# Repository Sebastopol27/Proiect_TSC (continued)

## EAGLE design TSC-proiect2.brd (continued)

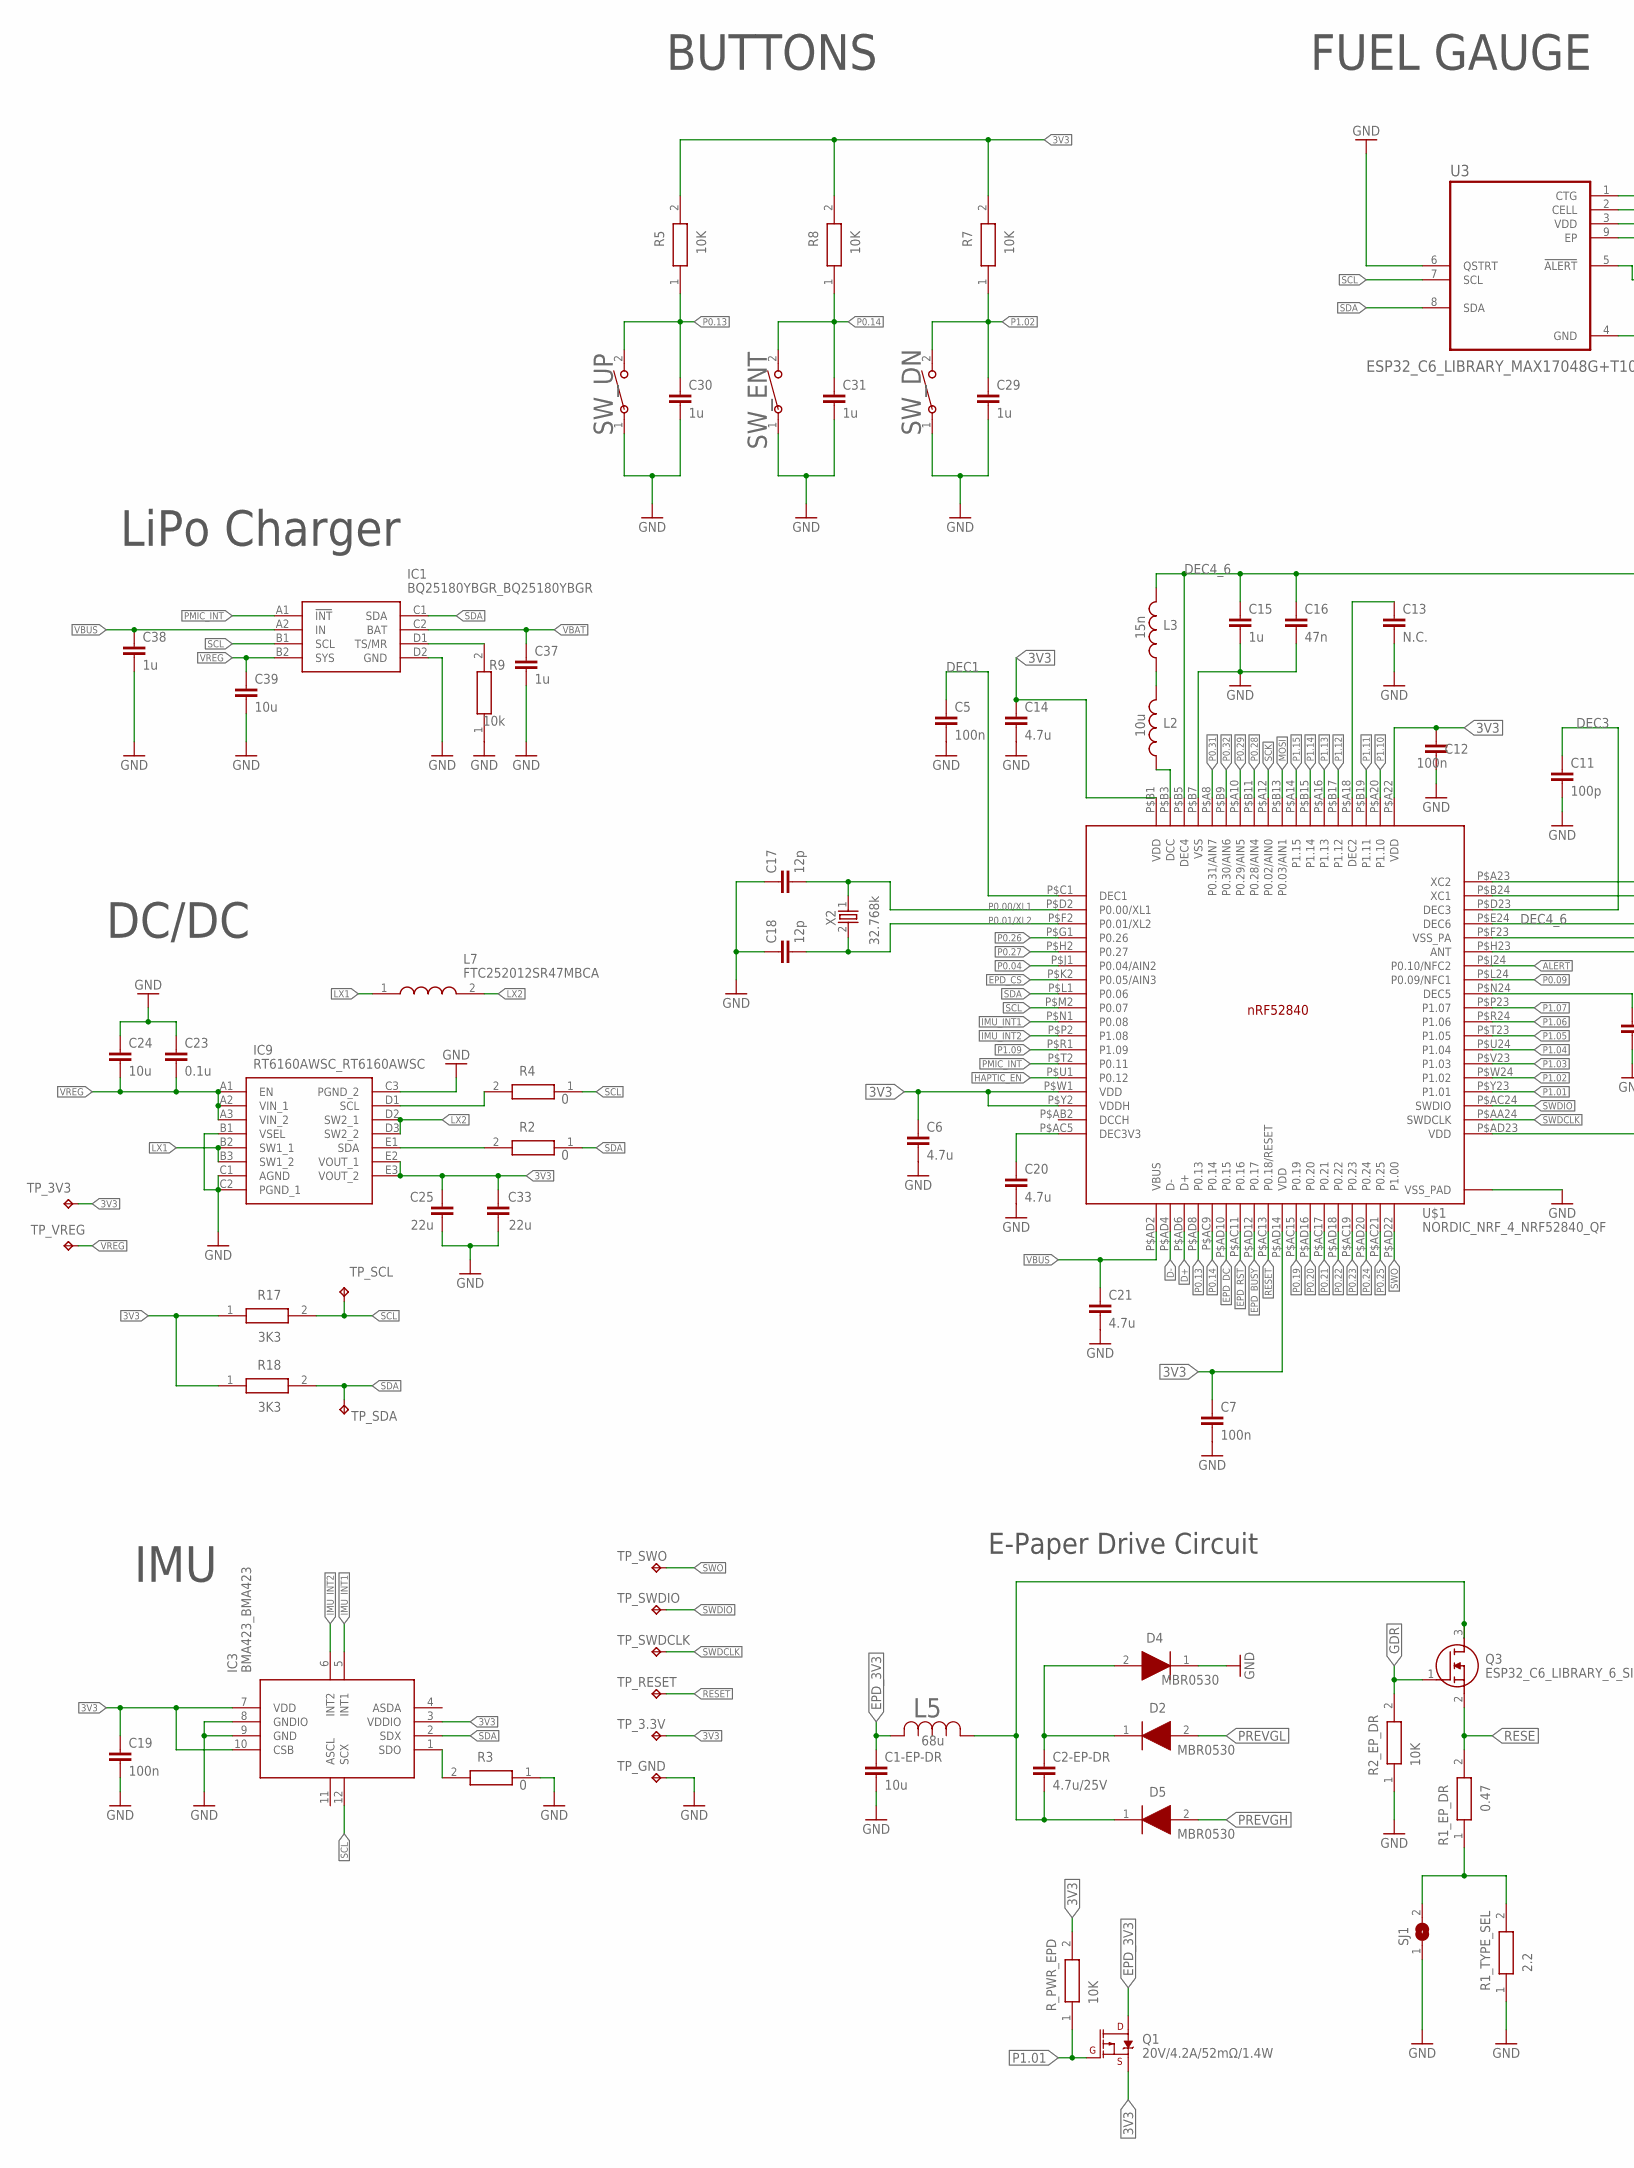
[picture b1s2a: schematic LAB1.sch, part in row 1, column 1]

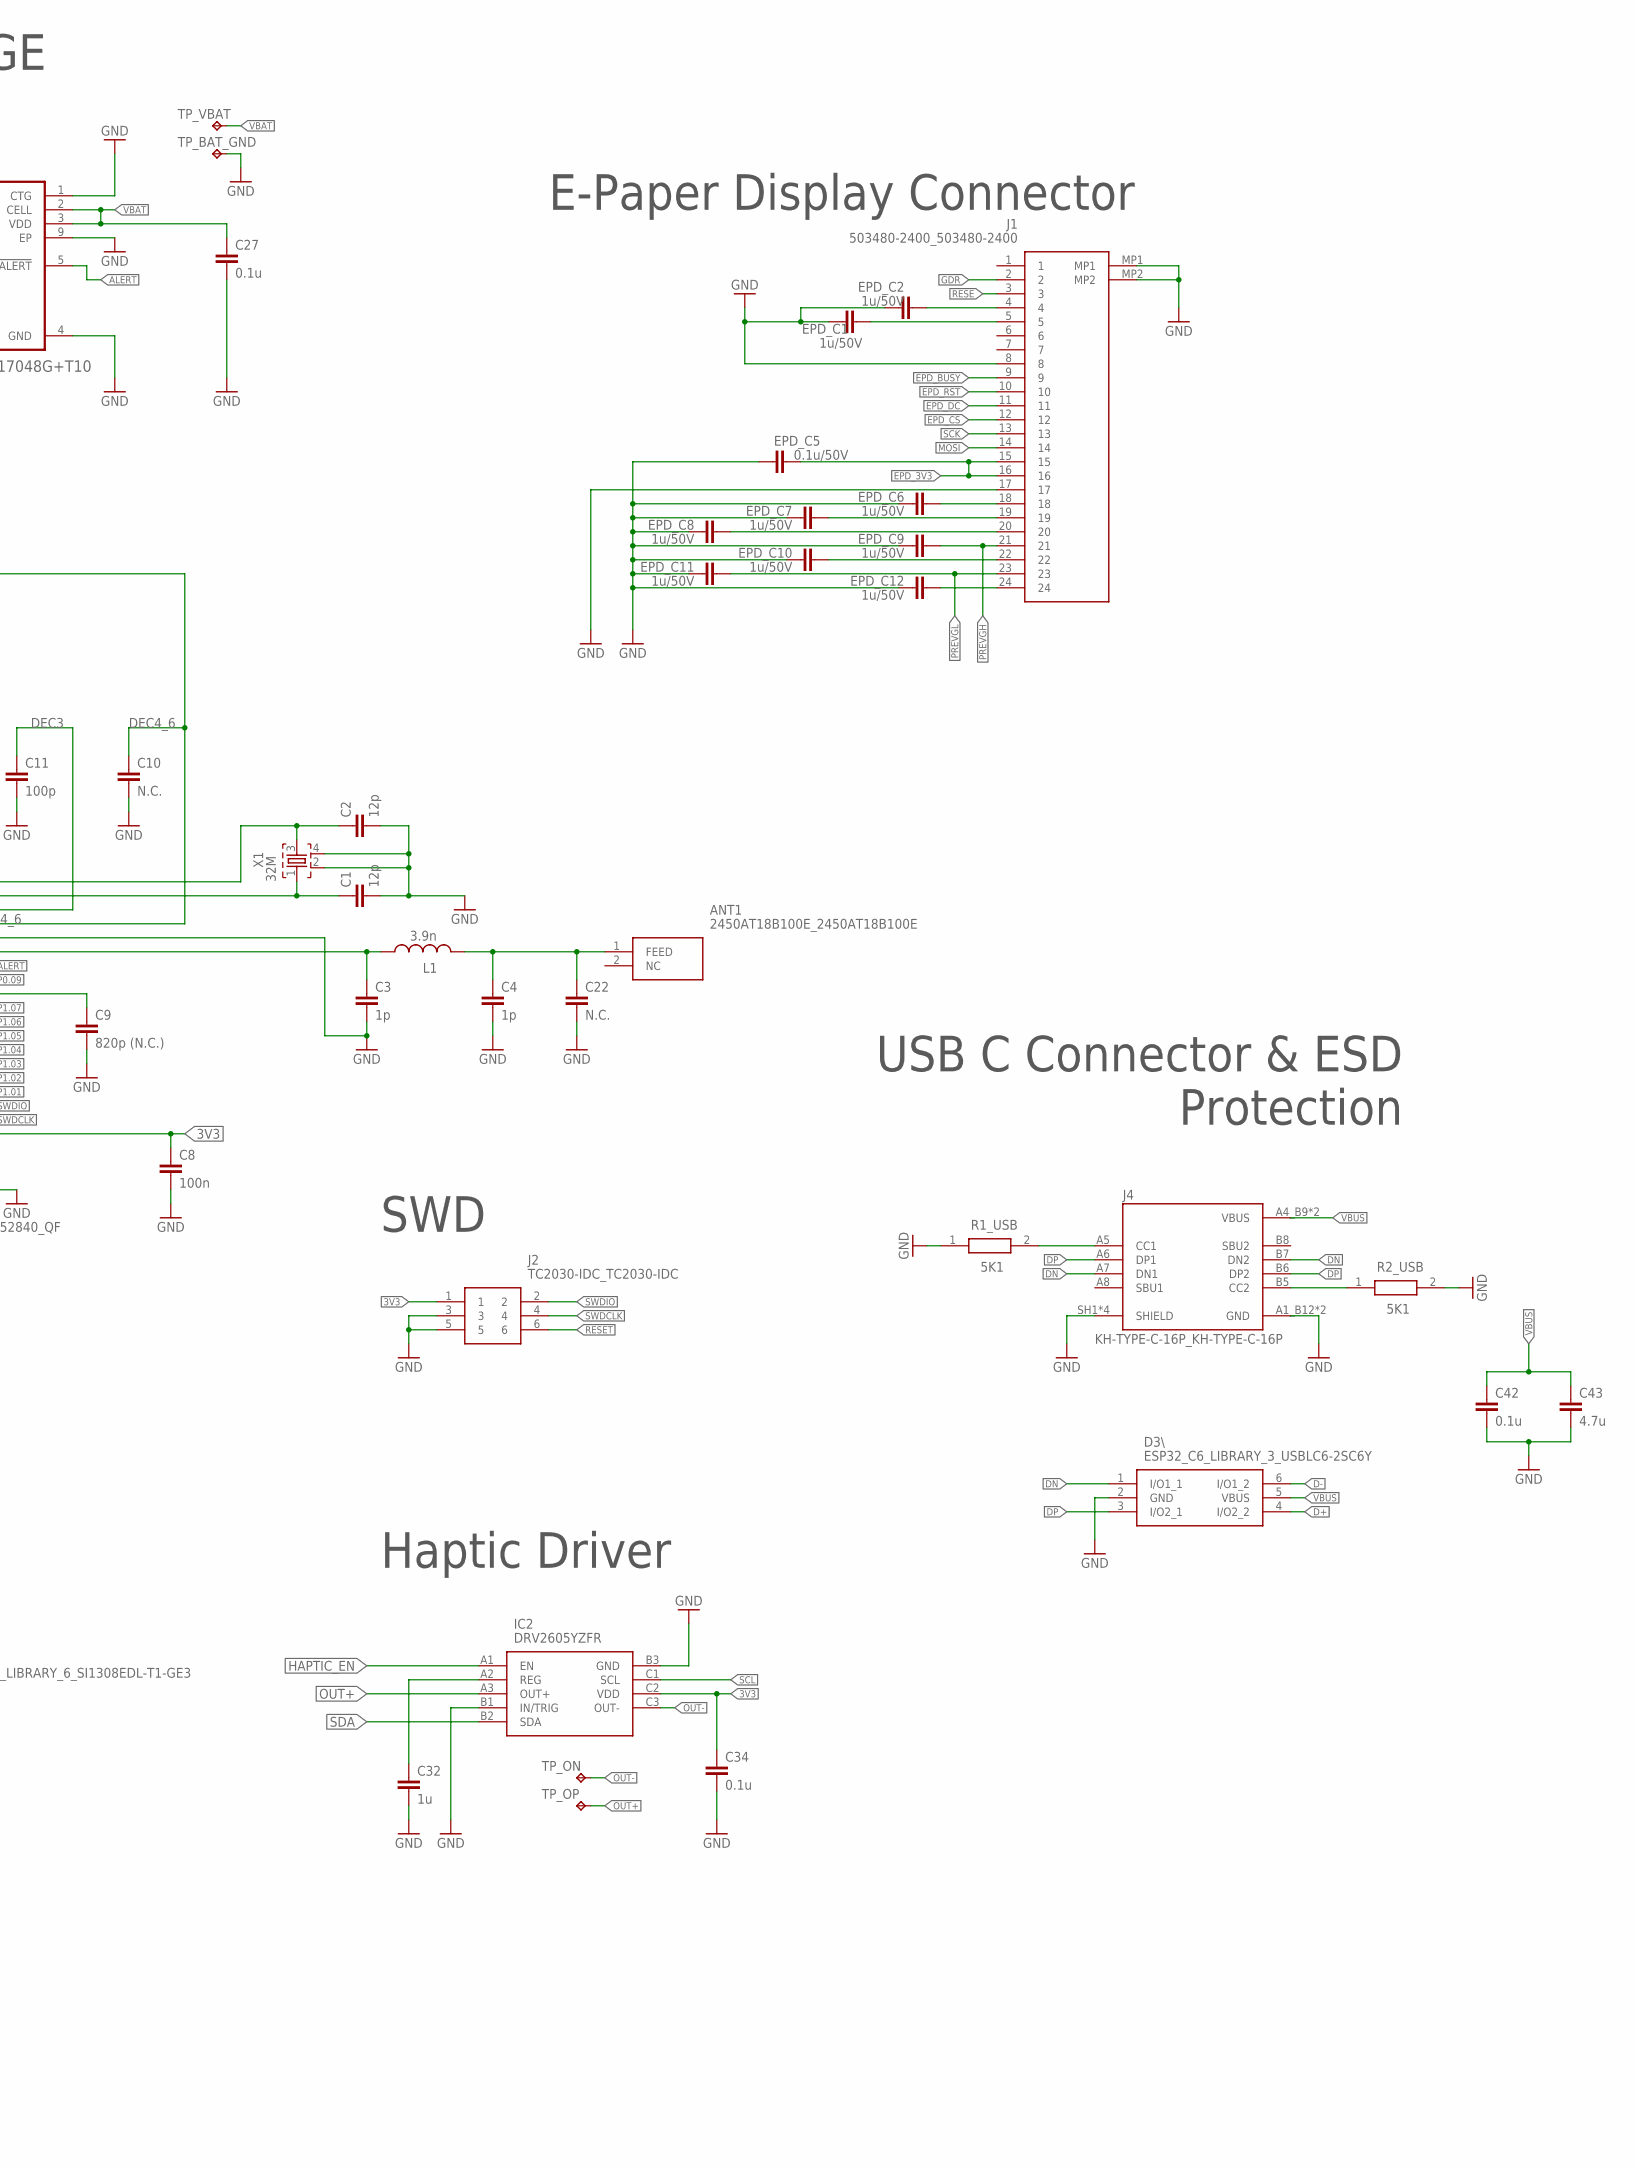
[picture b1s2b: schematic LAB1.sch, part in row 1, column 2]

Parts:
ANT1: 2450AT18B100E_2450AT18B100E; 2450AT18B100E_ANTC3216X140N
C1, C2, C17, C18: 12p; NORDIC_NRF_3_RESC0201_L
C1-EP-DR, C24, C39: 10u; PERFECT_0402_0402
C2-EP-DR: 4.7u/25V; NORDIC_NRF_3_RESC0603_L
C3, C4: 1p; NORDIC_NRF_3_RESC0201_L
C5, C7, C8, C12, C19: 100n; NORDIC_NRF_3_RESC0201_L
C6, C14, C20, C21, C43: 4.7u; PERFECT_0402_0402
C9: 820p (N.C.); NORDIC_NRF_3_RESC0201_L
C10, C22: N.C.; NORDIC_NRF_3_RESC0201_L
C11: 100p; NORDIC_NRF_3_RESC0201_L
C13: N.C.; PERFECT_0402_0402
C15, C29, C30, C31, C32, C37, C38: 1u; PERFECT_0402_0402
C16: 47n; NORDIC_NRF_3_RESC0201_L
C23, C27, C34, C42: 0.1u; NORDIC_NRF_3_RESC0201_L
C25: 22u; NORDIC_NRF_3_RESC0201_L
C33: 22u; PERFECT_0402_0402
D2, D4, D5: MBR0530; ESP32_C6_LIBRARY_5_SOD3716X135N
D3\: ESP32_C6_LIBRARY_3_USBLC6-2SC6Y; ESP32_C6_LIBRARY_3_SOT95P280X145-6N
EPD_C1, EPD_C2, EPD_C6, EPD_C7, EPD_C8, EPD_C9, EPD_C10, EPD_C11, EPD_C12: 1u/50V; NORDIC_NRF_3_RESC0603_L
EPD_C5: 0.1u/50V; NORDIC_NRF_3_RESC0603_L
IC1: BQ25180YBGR_BQ25180YBGR; BQ25180YBGR_BGA8C40P2X4_100X155X50
IC2: DRV2605YZFR; DRV2605YZFR_BGA9C50P3X3_144X144X62
IC3: BMA423_BMA423
IC9: RT6160AWSC_RT6160AWSC; RT6160AWSC_BGA15C40P3X5_140X230X60
J1: 503480-2400_503480-2400; 503480-2400_5034802400
J2: TC2030-IDC_TC2030-IDC; TC2030-IDC_TC2030IDC
J4: KH-TYPE-C-16P_KH-TYPE-C-16P; KH-TYPE-C-16P_KINGHELM_KH-TYPE-C-16P
L1: 3.9n; NORDIC_NRF_2_RESC0201_L
L2: 10u; NORDIC_NRF_2_RESC0402_L
L3: 15n; NORDIC_NRF_2_RESC0201_L
L5: 68u; ESP32_C6_LIBRARY_2_IND_4828-WE-TPC_WRE
L7: FTC252012SR47MBCA; MLP2016SR47MT0S1_INDC2016X100N
Q1: 20V/4.2A/52mΩ/1.4W; ESP32_C6_LIBRARY_4_ESP32_C6_LIBRARY_4_ESP32_C6_LIBRARY_4_ES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
Q3: ESP32_C6_LIBRARY_6_SI1308EDL-T1-GE3; ESP32_C6_LIBRARY_6_SOT65P210X110-3N
R1_EP_DR: 0.47; CPF0201D7K68C1_0201
R1_TYPE_SEL: 2.2; CPF0201D7K68C1_0201
R1_USB, R2_USB: 5K1; CPF0201D7K68C1_0201
R2, R3, R4: 0; CPF0201D7K68C1_0201
R2_EP_DR, R5, R7, R8: 10K; CPF0201D7K68C1_0201
R9: 10k; CPF0201D7K68C1_0201
R17, R18: 3K3; CPF0201D7K68C1_0201
R_PWR_EPD: 10K; CPF0201D7K68C1_0201
SJ1: ESP32_C6_LIBRARY_7_JUMPER_SJ
SW_DN: 2025-10-22_07-23-44_LIBRARY_EVP-AKE31ASW_EVP-AKE3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; 2025-10-22_07-23-44_LIBRARY_SW_EVP-AKE31A_PAN
SW_ENT: 2025-10-22_07-23-44_LIBRARY_EVP-AKE31ASW_EVP-AKE3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; 2025-10-22_07-23-44_LIBRARY_SW_EVP-AKE31A_PAN
SW_UP: 2025-10-22_07-23-44_LIBRARY_EVP-AKE31ASW_EVP-AKE3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; 2025-10-22_07-23-44_LIBRARY_SW_EVP-AKE31A_PAN
TP_3.3V, TP_3V3: HECTOR_WATCH_1_TPTP20R; HECTOR_WATCH_1_TP20R
TP_BAT_GND: HECTOR_WATCH_1_TPTP20R; HECTOR_WATCH_1_TP20R
TP_GND: HECTOR_WATCH_1_TPTP20R; HECTOR_WATCH_1_TP20R
TP_ON: HECTOR_WATCH_1_TPTP20R; HECTOR_WATCH_1_TP20R
TP_OP: HECTOR_WATCH_1_TPTP20R; HECTOR_WATCH_1_TP20R
TP_RESET: HECTOR_WATCH_1_TPTP20R; HECTOR_WATCH_1_TP20R
TP_SCL: HECTOR_WATCH_1_TPTP20R; HECTOR_WATCH_1_TP20R
TP_SDA: HECTOR_WATCH_1_TPTP20R; HECTOR_WATCH_1_TP20R
TP_SWDCLK: HECTOR_WATCH_1_TPTP20R; HECTOR_WATCH_1_TP20R
TP_SWDIO: HECTOR_WATCH_1_TPTP20R; HECTOR_WATCH_1_TP20R
TP_SWO: HECTOR_WATCH_1_TPTP20R; HECTOR_WATCH_1_TP20R
TP_VBAT: HECTOR_WATCH_1_TPTP20R; HECTOR_WATCH_1_TP20R
TP_VREG: HECTOR_WATCH_1_TPTP20R; HECTOR_WATCH_1_TP20R
U3: ESP32_C6_LIBRARY_MAX17048G+T10; ESP32_C6_LIBRARY_SON50P200X200X80-9N
U$1: NORDIC_NRF_4_NRF52840_QF; NORDIC_NRF_4_AQFN50P700X700X85_HS-74N
X1: 32M; NORDIC_NRF_BT-XTAL_2016_N
X2: 32.768k; NORDIC_NRF_1_XTAL_3215_N

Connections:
ALERT: U3.5 (!ALERT), U$1.P$J24 (P0.10/NFC2)
D+: D3\.4 (I/O2_2), U$1.P$AD6 (D+)
D-: D3\.6 (I/O1_2), U$1.P$AD4 (D-)
DEC1: C5.1, U$1.P$C1 (DEC1)
DEC3: C11.1, U$1.P$D23 (DEC3)
DEC4_6: C10.1, C15.1, C16.1, L3.2, U$1.P$B5 (DEC4), U$1.P$E24 (DEC6)
DN: D3\.1 (I/O1_1), J4.A7 (DN1), J4.B7 (DN2)
DP: D3\.3 (I/O2_1), J4.A6 (DP1), J4.B6 (DP2)
EPD_3V3: C1-EP-DR.1, EPD_C5.2, J1.15, J1.16, L5.2, Q1.3 (D)
EPD_BUSY: J1.9, U$1.P$AD12 (P0.17)
EPD_CS: J1.12, U$1.P$K2 (P0.05/AIN3)
EPD_DC: J1.11, U$1.P$AD10 (P0.15)
EPD_RST: J1.10, U$1.P$AC11 (P0.16)
GDR: J1.2, Q3.1 (G), R2_EP_DR.2
GND: C1.2, C1-EP-DR.2, C2.2, C3.2, C4.2, C5.2, C6.2, C7.2, C8.2, C9.2, C10.2, C11.2, C12.2, C13.2, C14.2, C15.2, C16.2, C17.1, C18.1, C19.2, C20.2, C21.2, C22.2, C23.1, C24.1, C25.1, C27.2, C29.2, C30.2, C31.2, C32.2, C33.1, C34.2, C37.2, C38.2, C39.2, C42.2, C43.2, D3\.2 (GND), D4.1 (K), EPD_C1.1, EPD_C2.1, EPD_C5.1, EPD_C6.1, EPD_C7.1, EPD_C8.1, EPD_C9.1, EPD_C10.1, EPD_C11.1, EPD_C12.1, IC1.D2 (GND), IC2.B1 (IN/TRIG), IC2.B3 (GND), IC3.8 (GNDIO), IC3.9 (GND), IC9.B1 (VSEL), IC9.C1 (AGND), IC9.C2 (PGND_1), IC9.C3 (PGND_2), J1.8, J1.17, J1.MP1, J1.MP2, J2.3, J2.5, J4.A1_B12 (GND), J4.A12_B1 (GND), J4.SH1 (SHIELD), J4.SH2 (SHIELD), J4.SH3 (SHIELD), J4.SH4 (SHIELD), R1_TYPE_SEL.1, R1_USB.1, R2_EP_DR.1, R2_USB.2, R3.1, R9.1, SJ1.1, SW_DN.1, SW_ENT.1, SW_UP.1, TP_BAT_GND.TP, TP_GND.TP, U3.1 (CTG), U3.4 (GND), U3.6 (QSTRT), U3.9 (EP), U$1.P$74 (VSS_PAD), U$1.P$75 (VSS_PAD), U$1.P$76 (VSS_PAD), U$1.P$77 (VSS_PAD), U$1.P$78 (VSS_PAD), U$1.P$79 (VSS_PAD), U$1.P$80 (VSS_PAD), U$1.P$81 (VSS_PAD), U$1.P$82 (VSS_PAD), U$1.P$83 (VSS_PAD), U$1.P$84 (VSS_PAD), U$1.P$85 (VSS_PAD), U$1.P$86 (VSS_PAD), U$1.P$87 (VSS_PAD), U$1.P$88 (VSS_PAD), U$1.P$89 (VSS_PAD), U$1.P$90 (VSS_PAD), U$1.P$B7 (VSS), U$1.P$F23 (VSS_PA), X1.2, X1.4
HAPTIC_EN: IC2.A1 (EN), U$1.P$U1 (P0.12)
IMU_INT1: IC3.5 (INT1), U$1.P$N1 (P0.08)
IMU_INT2: IC3.6 (INT2), U$1.P$P2 (P1.08)
LX1: IC9.B2 (SW1_1), IC9.B3 (SW1_2), L7.1
LX2: IC9.D2 (SW2_1), IC9.D3 (SW2_2), L7.2
MOSI: J1.14, U$1.P$B13 (P0.03/AIN1)
unnamed: L2.1, U$1.P$B3 (DCC)
unnamed: L2.2, L3.1
unnamed: C13.1, U$1.P$A18 (DEC2)
unnamed: C20.1, U$1.P$AC5 (DEC3V3)
unnamed: C9.1, U$1.P$N24 (DEC5)
unnamed: C3.1, L1.1, U$1.P$H23 (ANT)
unnamed: ANT1.1 (FEED), C4.1, C22.1, L1.2
unnamed: C1.1, U$1.P$B24 (XC1), X1.1
unnamed: C2.1, U$1.P$A23 (XC2), X1.3
unnamed: IC1.D1 (TS/MR), R9.2
unnamed: IC9.D1 (SCL), R4.2
unnamed: IC9.E1 (SDA), R2.2
unnamed: R17.1, R18.1
unnamed: R1_EP_DR.1, R1_TYPE_SEL.2, SJ1.2
unnamed: C32.1, IC2.A2 (REG)
unnamed: C2-EP-DR.1, D2.1 (K), D4.2 (A)
unnamed: C2-EP-DR.2, D5.1 (K), L5.1, Q3.3 (D)
unnamed: IC3.1 (SDO), R3.2
unnamed: EPD_C6.2, J1.18
unnamed: EPD_C7.2, J1.19
unnamed: EPD_C2.2, J1.4
unnamed: EPD_C1.2, J1.5
unnamed: EPD_C8.2, J1.20
unnamed: EPD_C10.2, J1.22
unnamed: EPD_C12.2, J1.24
unnamed: J4.B5 (CC2), R2_USB.1
unnamed: J4.A5 (CC1), R1_USB.2
OUT+: IC2.A3 (OUT+), TP_OP.TP
OUT-: IC2.C3 (OUT-), TP_ON.TP
P0.00/XL1: C17.2, U$1.P$D2 (P0.00/XL1), X2.1
P0.01/XL2: C18.2, U$1.P$F2 (P0.01/XL2), X2.2
P0.04: U$1.P$J1 (P0.04/AIN2)
P0.09: U$1.P$L24 (P0.09/NFC1)
P0.13: C30.1, R5.1, SW_UP.2, U$1.P$AD8 (P0.13)
P0.14: C31.1, R8.1, SW_ENT.2, U$1.P$AC9 (P0.14)
P0.19: U$1.P$AC15 (P0.19)
P0.20: U$1.P$AD16 (P0.20)
P0.21: U$1.P$AC17 (P0.21)
P0.22: U$1.P$AD18 (P0.22)
P0.23: U$1.P$AC19 (P0.23)
P0.24: U$1.P$AD20 (P0.24)
P0.25: U$1.P$AC21 (P0.25)
P0.26: U$1.P$G1 (P0.26)
P0.27: U$1.P$H2 (P0.27)
P0.28: U$1.P$B11 (P0.28/AIN4)
P0.29: U$1.P$A10 (P0.29/AIN5)
P0.31: U$1.P$A8 (P0.31/AIN7)
P0.32: U$1.P$B9 (P0.30/AIN6)
P1.01: Q1.1 (G), R_PWR_EPD.1, U$1.P$Y23 (P1.01)
P1.02: C29.1, R7.1, SW_DN.2, U$1.P$W24 (P1.02)
P1.03: U$1.P$V23 (P1.03)
P1.04: U$1.P$U24 (P1.04)
P1.05: U$1.P$T23 (P1.05)
P1.06: U$1.P$R24 (P1.06)
P1.07: U$1.P$P23 (P1.07)
P1.09: U$1.P$R1 (P1.09)
P1.10: U$1.P$A20 (P1.10)
P1.11: U$1.P$B19 (P1.11)
P1.12: U$1.P$B17 (P1.12)
P1.13: U$1.P$A16 (P1.13)
P1.14: U$1.P$B15 (P1.14)
P1.15: U$1.P$A14 (P1.15)
PMIC_INT: IC1.A1 (!INT), U$1.P$T2 (P0.11)
PREVGH: D5.2 (A), EPD_C9.2, J1.21
PREVGL: D2.2 (A), EPD_C11.2, J1.23
RESE: J1.3, Q3.2 (S), R1_EP_DR.2
RESET: J2.6, TP_RESET.TP, U$1.P$AC13 (P0.18/RESET)
SCK: J1.13, U$1.P$A12 (P0.02/AIN0)
SWDCLK: J2.4, TP_SWDCLK.TP, U$1.P$AA24 (SWDCLK)
SWDIO: J2.2, TP_SWDIO.TP, U$1.P$AC24 (SWDIO)
SWO: TP_SWO.TP, U$1.P$AD22 (P1.00)
VBAT: C27.1, C37.1, IC1.C2 (BAT), TP_VBAT.TP, U3.2 (CELL), U3.3 (VDD)
VBUS: C21.1, C38.1, C42.1, C43.1, D3\.5 (VBUS), IC1.A2 (IN), J4.A4_B9 (VBUS), J4.A9_B4 (VBUS), U$1.P$AD2 (VBUS)
VREG: C23.2, C24.2, C39.1, IC1.B2 (SYS), IC9.A1 (EN), IC9.A2 (VIN_1), IC9.A3 (VIN_2), TP_VREG.TP

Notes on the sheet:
LiPo Charger
DC/DC
IMU
SWD
E-Paper Drive Circuit
Haptic Driver
BUTTONS
FUEL GAUGE
E-Paper Display Connector
USB C Connector & ESD Protection

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
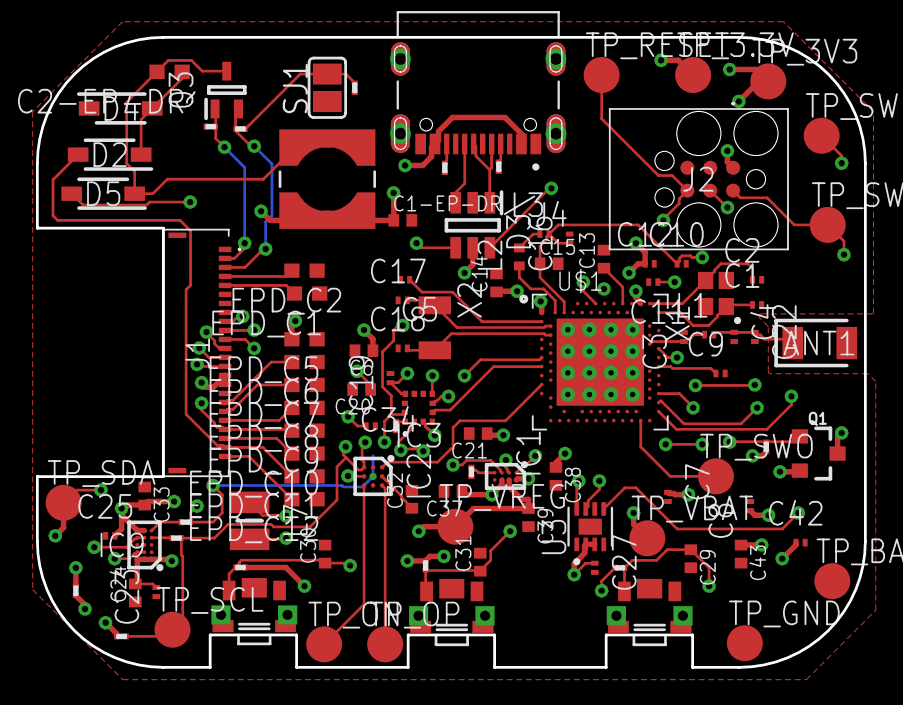
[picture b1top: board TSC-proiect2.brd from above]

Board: 4 copper layers, 46.0 x 35.0 mm, 105 parts (0 on the bottom side), 71 nets.

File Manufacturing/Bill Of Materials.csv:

Reference Designators;Quantity;Description;Package;Value;Manufacturer;Manufacturer Part Number;Vendor;Vendor Part Number;Top/Bottom;
;1;PCB Board;Board;;;;;;;
ANT1;1;Antennas 2.45GHz ANTENNA;2450AT18B100E_ANTC3216X140N;2450AT18B100E_2450AT18B100E;;;;;Top;
C1, C2, C17, C18;4;Generic chip capacitor;NORDIC_NRF_3_RESC0201_L;12p;;;;;Top;
C1-EP-DR, C24, C39;3;0402 (1005 Metric);PERFECT_0402_0402;10u;;;;;Top;
C2-EP-DR;1;Generic chip capacitor;NORDIC_NRF_3_RESC0603_L;4.7u/25V;;;;;Top;
C3, C4;2;Generic chip capacitor;NORDIC_NRF_3_RESC0201_L;1p;;;;;Top;
C5, C7, C8, C12, C19;5;Generic chip capacitor;NORDIC_NRF_3_RESC0201_L;100n;;;;;Top;
C6, C14, C20, C21, C43;5;0402 (1005 Metric);PERFECT_0402_0402;4.7u;;;;;Top;
C9;1;Generic chip capacitor;NORDIC_NRF_3_RESC0201_L;820p (N.C.);;;;;Top;
C10, C22;2;Generic chip capacitor;NORDIC_NRF_3_RESC0201_L;N.C.;;;;;Top;
C11;1;Generic chip capacitor;NORDIC_NRF_3_RESC0201_L;100p;;;;;Top;
C13;1;0402 (1005 Metric);PERFECT_0402_0402;N.C.;;;;;Top;
C15, C29, C30, C31, C32, C37, C38;7;0402 (1005 Metric);PERFECT_0402_0402;1u;;;;;Top;
C16;1;Generic chip capacitor;NORDIC_NRF_3_RESC0201_L;47n;;;;;Top;
C23, C27, C34, C42;4;Generic chip capacitor;NORDIC_NRF_3_RESC0201_L;0.1u;;;;;Top;
C25;1;Generic chip capacitor;NORDIC_NRF_3_RESC0201_L;22u;;;;;Top;
C33;1;0402 (1005 Metric);PERFECT_0402_0402;22u;;;;;Top;
D2, D4, D5;3;ON SEMICONDUCTOR - MBR0530 - DIODE, SCHOTTKY, 0.5A, 30V, SOD-123;SOD3716X135N;MBR0530;;;;;Top;
D3\;1;Low Cap. ESD Protection Auto SOT-23-6 STMicroelectronics USBLC6-2SC6Y, Dual Uni-Directional TVS Diode Array, 6-Pin SOT-23;SOT95P280X145-6N;ESP32_C6_LIBRARY_3_USBLC6-2SC6Y;;;;;Top;
EPD_C1, EPD_C2, EPD_C6, EPD_C7, EPD_C8, EPD_C9, EPD_C10, EPD_C11, EPD_C12;9;Generic chip capacitor;NORDIC_NRF_3_RESC0603_L;1u/50V;;;;;Top;
EPD_C5;1;Generic chip capacitor;NORDIC_NRF_3_RESC0603_L;0.1u/50V;;;;;Top;
IC1;1;Charger IC Lithium Ion/Polymer, Lithium Iron Phosphate 8-DSBGA (1.6x1.1);BQ25180YBGR_BGA8C40P2X4_100X155X50;BQ25180YBGR_BQ25180YBGR;;;;;Top;
IC2;1;Haptic Driver for ERM/LRA with Built-In Library and Smart Loop Architecture;DRV2605YZFR_BGA9C50P3X3_144X144X62;DRV2605YZFR;;;;;Top;
IC3;1;Accelerometers Triaxial low-g 12bit Acceleration Sensor;BMA423_BMA423;BMA423_BMA423;;;;;Top;
IC9;1;Buck-Boost Regulator Positive Output Step-Up/Step-Down I2C DC-DC Controller IC 15-WL-CSP (BSC) (1.4x2.3);RT6160AWSC_BGA15C40P3X5_140X230X60;RT6160AWSC_RT6160AWSC;;;;;Top;
J1;1;FFC & FPC Connectors 0.5mm FPC RA SMT Dual Contact 24Ckt;503480-2400_5034802400;503480-2400_503480-2400;;;;;Top;
J2;1;CABLE ADAPTER 6 POS;TC2030-IDC_TC2030IDC;TC2030-IDC_TC2030-IDC;;;;;Top;
J4;1;Check availability;KINGHELM_KH-TYPE-C-16P;KH-TYPE-C-16P_KH-TYPE-C-16P;;;;;Top;
L1;1;Generic chip inductor;NORDIC_NRF_2_RESC0201_L;3.9n;;;;;Top;
L2;1;Generic chip inductor;NORDIC_NRF_2_RESC0402_L;10u;;;;;Top;
L3;1;Generic chip inductor;NORDIC_NRF_2_RESC0201_L;15n;;;;;Top;
L5;1;;ESP32_C6_LIBRARY_2_IND_4828-WE-TPC_WRE;68u;;;;;Top;
L7;1;SMD / SMT Inductors (Coils), L=0.47?H, L x W x T :;MLP2016SR47MT0S1_INDC2016X100N;FTC252012SR47MBCA;;;;;Top;
Q1;1;P-channel MOSFETs;ESP32_WROVER_SPARKFUN-DISCRETESEMI_SOT23-3;20V/4.2A/52mΩ/1.4W;;;;;Top;
Q3;1;MOSFET N-Ch 30V 1.5A TrenchFET SC70 Vishay Si1308EDL-T1-GE3 N-channel MOSFET Transistor, 1.5 A, 30 V, 3-Pin SC-70;SOT65P210X110-3N;ESP32_C6_LIBRARY_6_SI1308EDL-T1-GE3;;;;;Top;
R_PWR_EPD, R2_EP_DR, R5, R7, R8;5;7.68k 0201 Thin Film Surface Mount Fixed Resistor +/-0.5% 0.031W CPF0201D7K68C1;CPF0201D7K68C1_0201;10K;;;;;Top;
R1_EP_DR;1;7.68k 0201 Thin Film Surface Mount Fixed Resistor +/-0.5% 0.031W CPF0201D7K68C1;CPF0201D7K68C1_0201;0.47;;;;;Top;
R1_TYPE_SEL;1;7.68k 0201 Thin Film Surface Mount Fixed Resistor +/-0.5% 0.031W CPF0201D7K68C1;CPF0201D7K68C1_0201;2.2;;;;;Top;
R1_USB, R2_USB;2;7.68k 0201 Thin Film Surface Mount Fixed Resistor +/-0.5% 0.031W CPF0201D7K68C1;CPF0201D7K68C1_0201;5K1;;;;;Top;
R2, R3, R4;3;7.68k 0201 Thin Film Surface Mount Fixed Resistor +/-0.5% 0.031W CPF0201D7K68C1;CPF0201D7K68C1_0201;0;;;;;Top;
R9;1;7.68k 0201 Thin Film Surface Mount Fixed Resistor +/-0.5% 0.031W CPF0201D7K68C1;CPF0201D7K68C1_0201;10k;;;;;Top;
R17, R18;2;7.68k 0201 Thin Film Surface Mount Fixed Resistor +/-0.5% 0.031W CPF0201D7K68C1;CPF0201D7K68C1_0201;3K3;;;;;Top;
SJ1;1;SMD solder JUMPER;JUMPER_SJ;;;;;;Top;
SW_DN, SW_ENT, SW_UP;3;;SW_EVP-AKE31A_PAN;2025-10-22_07-23-44_LIBRARY_EVP-AKE31ASW_EVP-AKE31A_PAN;;;;;Top;
TP_3.3V, TP_3V3, TP_BAT_GND, TP_GND, TP_ON, TP_OP, TP_RESET, TP_SCL, TP_SDA, TP_SWDCLK, TP_SWDIO, TP_SWO, TP_VBAT, TP_VREG;14;Test pad;HECTOR_WATCH_1_TP20R;HECTOR_WATCH_1_TPTP20R;;;;;Top;
U$1;1;nRF52840;NORDIC_NRF_4_AQFN50P700X700X85_HS-74N;NORDIC_NRF_4_NRF52840_QF;;;;;Top;
U3;1;Check availability;SON50P200X200X80-9N;ESP32_C6_LIBRARY_MAX17048G+T10;;;;;Top;
X1;1;;NORDIC_NRF_BT-XTAL_2016_N;32M;;;;;Top;
X2;1;;NORDIC_NRF_1_XTAL_3215_N;32.768k;;;;;Top;

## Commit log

2026-04-21 Enhance README with hardware details and BOM
    Added detailed hardware architecture, BOM, and functionality sections to the README.
